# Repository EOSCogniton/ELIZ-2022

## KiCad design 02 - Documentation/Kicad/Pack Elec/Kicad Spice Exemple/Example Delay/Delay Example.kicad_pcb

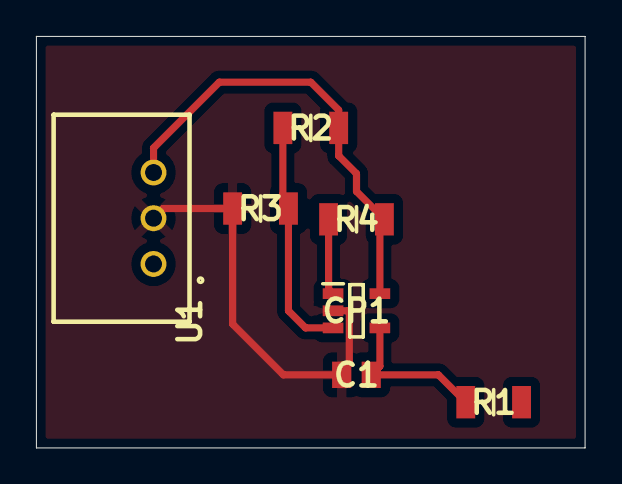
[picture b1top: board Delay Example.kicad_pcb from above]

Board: 2 copper layers, 30.5 x 22.9 mm, 7 parts (0 on the bottom side), 5 nets.

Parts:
C1: Condensateur 0805Y1000104JXT; CAPC2012X130N
CP1: Comparateur TS391ILT; SOT95P280X145-5N
R1, R2, R3, R4: Résistance RK73H2BLTDD2152F; RESC3216X70N
U1: Alim LP TSR_0.5-2450; TSR-0.5-2433

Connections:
0: C1.1, CP1.2 (VCC-), R3.1, U1.2 (GND)
unnamed: C1.2, CP1.4 (IN+), R1.1
unnamed: CP1.1 (OUT), R4.1
unnamed: CP1.3 (IN-), R2.1, R3.2
unnamed: CP1.5 (VCC+), R2.2, R4.2, U1.3 (+VOUT)

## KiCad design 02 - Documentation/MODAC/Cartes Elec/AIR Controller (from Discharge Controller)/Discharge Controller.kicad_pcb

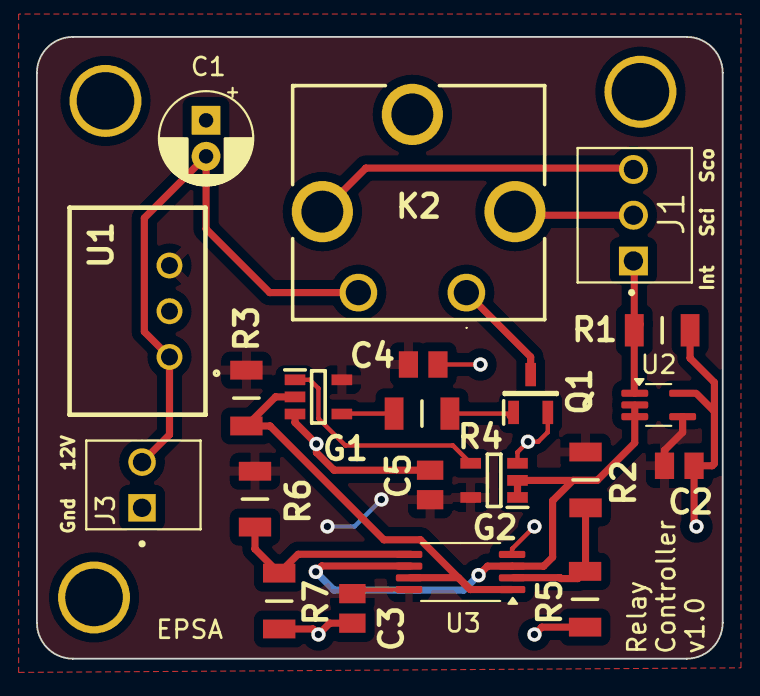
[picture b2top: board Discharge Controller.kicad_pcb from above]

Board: 2 copper layers, 38.1 x 34.5 mm, 21 parts (0 on the bottom side), 14 nets.

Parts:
C1: C; CP_Radial_D5.0mm_P2.00mm
C2, C3, C4, C5: 10n; CAPC2012X130N
G1: Gate AND SN74AHCT1G08DBVR; SOT95P280X145-5N
G2: Gate NAND SN74AHCT1G00DBVR; SOT95P280X145-5N
J1: 3P Droit 22-11-2032; MOLEX_22-11-2032
J3: 2P Droit 2-11-2022; MOLEX_22-11-2022
K2: Relais PCB; CP112V
Q1: NMOS SQ2348ES-T1_GE3; SOT95P237X112-3N
R1: 500k; RESC3216X70N
R2, R7: 82k; RESC3216X70N
R3: 10k; RESC3216X70N
R4: 1k; RESC3216X70N
R5, R6: 12k; RESC3216X70N
U1: Alim LP TSR_0.5-2450; TSR-0.5-2433
U2: SOT-353_SC-70-5_Handsoldering
U3: Opamp_Dual; TSSOP-8_4.4x3mm_P0.65mm

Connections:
+5V: C2.2, C3.2, C4.2, C5.2, G1.5 (VCC), G2.5 (VCC), R2.2, R3.1, R6.2, U1.3 (+VOUT), U2.4 (V+), U3.8 (V+)
+12V: C1.2, J3.2, K2.5, U1.1 (+VIN)
/0.75V: R2.1, R5.2, U3.2 (-)
/4.25V: R6.1, R7.2, U3.5 (+)
/Raw_Relay_Closed: J1.1, R1.1, U2.1 (+)
/Relay_Closed: G2.1, G2.2, U2.2 (-), U2.3, U3.3 (+), U3.6 (-)
/SC in: J1.2, K2.2
/SC out: J1.3, K2.4
/SCS_Compliance: G1.2, R3.2, U3.1, U3.7
GND: C1.1, C2.1, C3.1, C4.1, C5.1, G1.3 (GND), G2.3 (GND), J3.1, Q1.2, R1.2, R5.1, R7.1, U1.2 (GND), U2.5 (V-), U3.4 (V-)
unnamed: G1.1, G2.4
unnamed: G1.4, R4.1
unnamed: K2.1, Q1.3
unnamed: Q1.1, R4.2

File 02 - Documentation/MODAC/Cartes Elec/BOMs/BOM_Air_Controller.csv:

"Reference","Value","Qty","Manufacturer_Name","Manufacturer_Part_Number","Description"
"C1","C","1","","",""
"C2,C3,C4,C5","10n","4","Syfer","0805Y1000104JXT","Syfer 0805 Ceramic Chip Capacitors"
"G1,G2","Gate AND SN74AHCT1G08DBVR","2","Texas Instruments","SN74AHCT1G08DBVR","SN74AHCT1G08DBVR, Logic Gate 2 Input AND, AHCT, 8mA 5V 5-Pin SOT-23"
"J1","3P Droit 22-11-2032","1","Molex","22-11-2032",""
"J3","2P Droit 22-11-2022","1","Molex","22-11-2022",""
"K2","Relais PCB","1","Panasonic","CP1-12V","PANASONIC ELECTRIC WORKS - CP1-12V - RELAY, AUTOMOTIVE, SPDT, 14VDC, 20A"
"Q1","NMOS SQ2348ES-T1_GE3","1","Vishay","SQ2348ES-T1_GE3","VISHAY - SQ2348ES-T1_GE3 - MOSFET, AEC-Q101, N-CH, 30V, SOT-23"
"R1","500k","1","KOA Speer","RK73H2BLTDD2152F","Thick Film Resistors - SMD"
"R2,R7","82k","2","KOA Speer","RK73H2BLTDD2152F","Thick Film Resistors - SMD"
"R3","10k","1","KOA Speer","RK73H2BLTDD2152F","Thick Film Resistors - SMD"
"R4","1k","1","KOA Speer","RK73H2BLTDD2152F","Thick Film Resistors - SMD"
"R5,R6","12k","2","KOA Speer","RK73H2BLTDD2152F","Thick Film Resistors - SMD"
"U1","Alim LP TSR_0.5-2450","1","Traco Power","TSR 0.5-2450","0.5 Amp POL switching regulator, 4.75 to -32 VDC input, pos.-pos. circuit, LM78 compatible, SIP-3"
"U2","","1","Texas Instruments","TLV9061QDCKRQ1","Operational amplifier, single, node sequence=1:+ 2:- 3:OUT 4:V+ 5:V-"
"U3","Opamp_Dual","1","Texas Instruments","LMV393IPWR","Dual comparator"

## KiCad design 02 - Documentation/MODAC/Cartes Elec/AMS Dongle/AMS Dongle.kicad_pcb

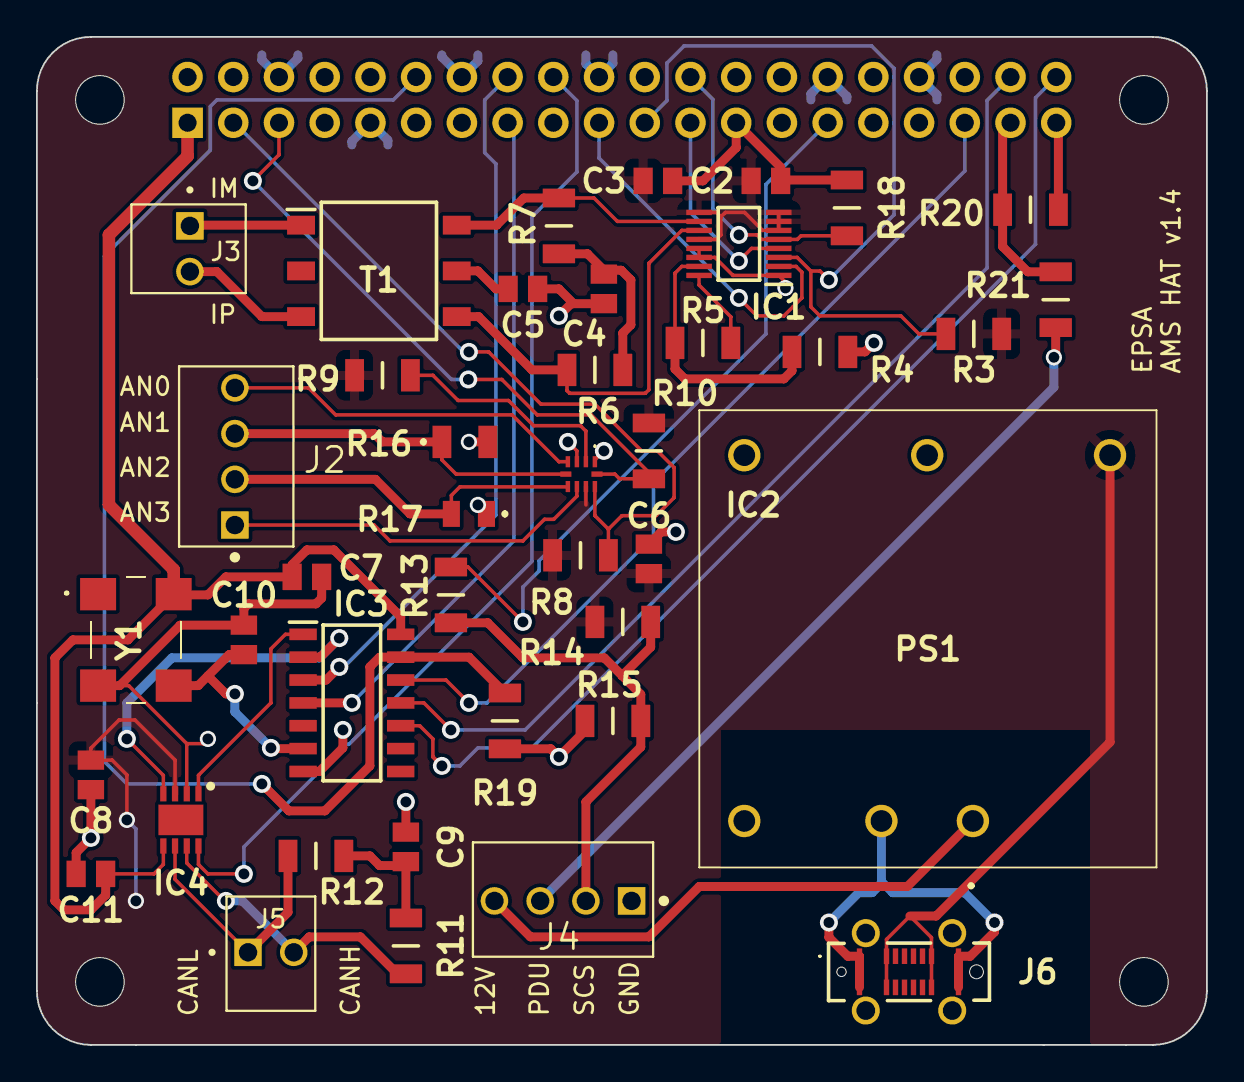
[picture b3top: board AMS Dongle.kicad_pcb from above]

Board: 2 copper layers, 65.0 x 56.0 mm, 46 parts (1 on the bottom side), 41 nets.

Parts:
C2, C3, C6, C7, C8, C11: 100n; CAPC2012X130N
C4, C5: 10n; CAPC2012X130N
C9: 4.7n; CAPC2012X130N
C10: 22p; CAPC2012X130N
IC1: LTC6820HMS#PBF; SOP50P490X110-16N
IC2: ADC I2C ADS1115QNKSRQ1; ADS1115QNKSRQ1
IC3: CAN Controller MCP2518FDT-H_SL; SOIC127P600X175-14N
IC4: CAN Transceiver ATA6563-GBQW1; SON65P300X300X90-9N-D
J1: GPIO; PinSocket_2x20_P2.54mm_Vertical
J2, J4: 4P Angle 171857-4004; MOLEX_22-11-2042
J3, J5: 2P Angle 171857-4002; MOLEX_22-11-2022
J6: UJ20-C-V-C-1-SMT-TR; UJ20CVC1SMTTR
MH1, MH2, MH3, MH4: MountingHole_2.7mm_M2.5
PS1: Alim; THN301211
R3, R8, R9, R10: 2k; RESC3216X70N
R4, R5: 1k; RESC3216X70N
R6, R7: 51; RESC3216X70N
R11, R12: 60; RESC3216X70N
R13: 3k9; RESC3216X70N
R14, R15: 8k2; RESC3216X70N
R16: 24 .5W; RCS1206_E3
R17: 47 .5W; RCS0805_E3
R18, R19: 360; RESC3216X70N
R20: 3.6k; RESC3216X70N
R21: 10k; RESC3216X70N
T1: SM91502ALE; SOP254P927X572-6N
Y1: Oscillateur CB3-3C-20M0000; CB3LV3C20M0000

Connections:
+3V3: C7.1, C11.1, IC3.14 (VDD), IC4.5 (VIO), J1.1, J1.17, Y1.4 (VCC)
+5V: C2.1, C3.1, C6.1, C8.2, IC1.6 (VDDS), IC1.7 (POL), IC1.8 (PHA), IC1.9 (VDD), IC1.12 (MSTR), IC2.8 (VDD), IC4.3 (VCC), J6.A4 (VBUS_1), J6.A9 (VBUS_2), J6.B4 (VBUS_3), J6.B9 (VBUS_4), PS1.3 (+VOUT), R3.1, R8.2, R9.1, R10.2, R14.2
+5VP: J1.2, J1.4
+12V: J4.4, PS1.1 (+VIN_(VCC))
/AN0: IC2.4 (AIN0), J2.4
/AN1: IC2.5 (AIN1), J2.3, R16.1
/AN2: IC2.6 (AIN2), J2.2, R17.2
/AN3: IC2.7 (AIN3), J2.1
/CANH: IC4.7 (CANH), J5.2, R11.2
/CANL: IC4.6 (CANL), J5.1, R12.2
/GPIO2/SDA1: IC2.9 (SDA), J1.3, R8.1
/GPIO3/SCL1: IC2.10 (SCL), J1.5, R10.1
/GPIO5: J1.29, R13.2
/GPIO8/SPI0.CE0: IC1.5 (~CS), J1.24, R18.2
/GPIO9/SPI0.MISO: IC1.3 (MISO), J1.21, R3.2
/GPIO10/SPI0.MOSI: IC1.2 (MOSI), J1.19
/GPIO11/SPI0.SCLK: IC1.4 (SCK), J1.23
/GPIO18/PCM.CLK/SPI1.CE0: IC3.13 (NCS), J1.12, R19.1
/GPIO19/PCM.FS/SPI1.MISO: IC3.12 (SDO), J1.35
/GPIO20/PCM.DIN/SPI1.MOSI: IC3.11 (SDI), J1.38
/GPIO21/PCM.DOUT/SPI1.SCLK: IC3.10 (SCK), J1.40
/GPIO22: IC3.4 (~INT), J1.15
/GPIO23: IC3.3 (CLKO/SOF), J1.16
/GPIO24: IC4.8 (STBY), J1.18
/GPIO26: J1.37, R20.2, R21.1
/IM: J3.1, T1.1 (PRI_1)
/IP: J3.2, T1.3 (PRI_3)
/PDU: J4.3, R21.2
/SCS Out: J4.2, R13.1, R14.1, R15.2
GND: C2.2, C3.2, C4.1, C5.2, C6.2, C7.2, C8.1, C9.2, C10.2, C11.2, IC1.1 (EN), IC1.13 (SLOW), IC1.14 (GND), IC2.1 (ADDR), IC2.3 (GND), IC3.7 (VSS), IC4.2 (GND), J1.6, J1.9, J1.14, J1.20, J1.25, J1.30, J1.34, J1.39, J4.1, J6.A1 (GND_1), J6.A12 (GND_2), J6.B1 (GND_3), J6.B12 (GND_4), PS1.2 (-VIN_(GND)), PS1.5 (-VOUT), R4.2, R15.1, R16.2, R17.1, R18.1, R19.2, R20.1, Y1.2 (GND)
unnamed: C4.2, R6.2, R7.1
unnamed: C9.1, R11.1, R12.1
unnamed: IC1.16 (IBIAS), R5.2
unnamed: IC1.15 (ICMP), R4.1, R5.1
unnamed: IC1.10 (IM), R7.2, T1.6 (SEC_3)
unnamed: IC1.11 (IP), R6.1, T1.4 (SEC_1)
unnamed: IC2.2 (ALERT/RDY), R9.2
unnamed: C10.1, IC3.6 (OSC1), Y1.3 (OUTPUT)
unnamed: IC3.2 (RXCAN), IC4.4 (RXD)
unnamed: IC3.1 (TXCAN), IC4.1 (TXD)
unnamed: C5.1, T1.5 (SEC_2)

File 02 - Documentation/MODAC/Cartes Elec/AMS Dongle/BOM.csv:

"Reference","Value","Manufacturer_Name","Manufacturer_Part_Number","Mouser Part Number","Mouser Price/Stock","Qty"
"C2,C3,C6,C7,C8","100n","Syfer","0805Y1000104JXT","","","5"
"C4,C5","10n","Syfer","0805Y1000104JXT","","","2"
"C9","4.7n","Syfer","0805Y1000104JXT","","","1"
"C10","22p","Syfer","0805Y1000104JXT","","","1"
"IC1","LTC6820HMS#PBF","Analog Devices","LTC6820HMS#PBF","584-LTC6820HMS#PBF","https://www.mouser.co.uk/ProductDetail/Analog-Devices/LTC682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","1"
"IC2","ADC I2C ADS1115QNKSRQ1","Texas Instruments","ADS1115QNKSRQ1","595-ADS1115QNKSRQ1","https://www.mouser.co.uk/ProductDetail/Texas-Instruments/ADS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","1"
"IC3","CAN Controller MCP2518FDT-H_SL","Microchip","MCP2518FDT-H/SL","579-MCP2518FDT-H/SL","https://www.mouser.co.uk/ProductDetail/Microchip-Technology/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","1"
"IC4","CAN Transceiver BD41041FJ-CE2","ROHM Semiconductor","BD41041FJ-CE2","755-BD41041FJ-CE2","https://www.mouser.co.uk/ProductDetail/ROHM-Semiconductor/BD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","1"
"J1","GPIO","","","","","1"
"J2,J4","4P Angle 171857-4004","Molex","171857-4004","538-171857-4004","https://www.mouser.co.uk/ProductDetail/Molex/171857-4004?qs=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","2"
"J3,J5","2P Angle 171857-4002","Molex","171857-4002","538-171857-4002","https://www.mouser.co.uk/ProductDetail/Molex/171857-4002?qs=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","2"
"J6","Connecteur USB-C USB4720-03-A","GCT (GLOBAL CONNECTOR TECHNOLOGY)","USB4720-03-A","640-USB472003A","https://www.mouser.co.uk/ProductDetail/GCT/USB4720-03-A?qs=Z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","1"
"PS1","Alim","Traco Power","THN 30-1211","495-THN-30-1211","https://www.mouser.co.uk/ProductDetail/TRACO-Power/THN-30-12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","1"
"Q1","NMOS SQ2348ES-T1_GE3","Vishay","SQ2348ES-T1_GE3","781-SQ2348ES-T1_GE3","https://www.mouser.co.uk/ProductDetail/Vishay-Siliconix/SQ23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","1"
"R3,R8,R9,R10","2k","KOA Speer","RK73H2BLTDD2152F","N/A","https://www.mouser.co.uk/ProductDetail/KOA-Speer/RK73H2BLTDD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","4"
"R4","2.8k","KOA Speer","RK73H2BLTDD2152F","N/A","https://www.mouser.co.uk/ProductDetail/KOA-Speer/RK73H2BLTDD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","1"
"R5","1.21k","KOA Speer","RK73H2BLTDD2152F","N/A","https://www.mouser.co.uk/ProductDetail/KOA-Speer/RK73H2BLTDD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","1"
"R6,R7","51","KOA Speer","RK73H2BLTDD2152F","N/A","https://www.mouser.co.uk/ProductDetail/KOA-Speer/RK73H2BLTDD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","2"
"R11,R12","60","KOA Speer","RK73H2BLTDD2152F","N/A","https://www.mouser.co.uk/ProductDetail/KOA-Speer/RK73H2BLTDD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","2"
"R13","3k9","KOA Speer","RK73H2BLTDD2152F","N/A","https://www.mouser.co.uk/ProductDetail/KOA-Speer/RK73H2BLTDD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","1"
"R14,R15","8k2","KOA Speer","RK73H2BLTDD2152F","N/A","https://www.mouser.co.uk/ProductDetail/KOA-Speer/RK73H2BLTDD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","2"
"S1,S2","CAS-120B","Nidec Copal","CAS-120B","229-CAS-120B","https://www.mouser.co.uk/ProductDetail/Nidec-Copal/CAS-120B?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","2"
"T1","SM91502ALE","Bourns","SM91502ALE","652-SM91502ALE","https://www.mouser.co.uk/ProductDetail/Bourns/SM91502ALE?qs=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","1"
"Y1","Oscillateur CB3-3C-20M0000","CTS","CB3-3C-20M0000","774-CB3-3C-20M0","https://www.mouser.co.uk/ProductDetail/CTS-Electronic-Compon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","1"

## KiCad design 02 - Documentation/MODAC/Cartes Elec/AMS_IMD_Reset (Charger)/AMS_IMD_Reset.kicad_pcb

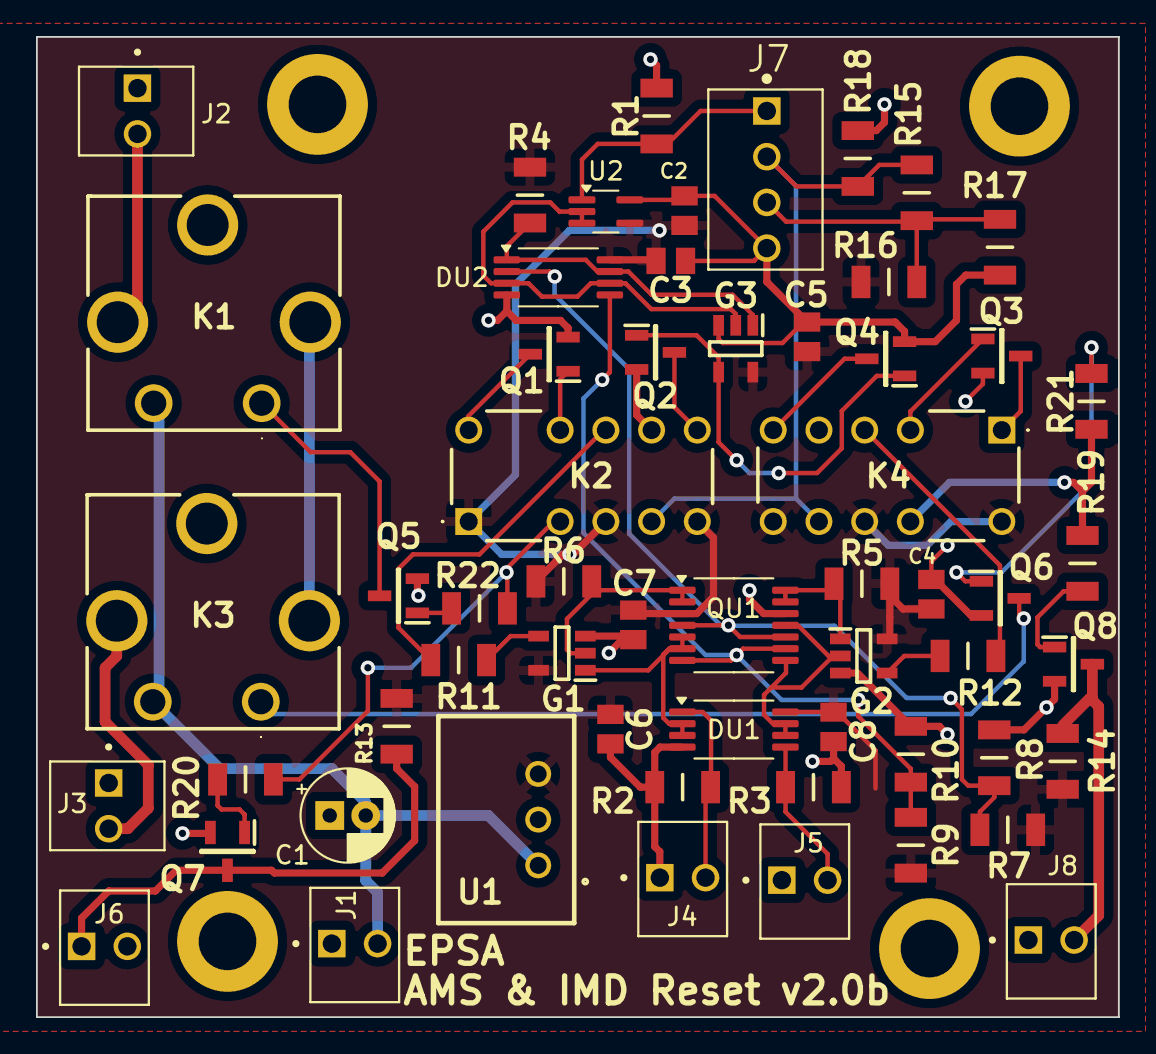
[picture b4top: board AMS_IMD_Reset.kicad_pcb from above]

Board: 2 copper layers, 60.1 x 54.5 mm, 58 parts (0 on the bottom side), 40 nets.

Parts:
C1: C; CP_Radial_D5.0mm_P2.00mm
C2, C3, C4, C5, C6, C7, C8: 1u; CAPC2012X130N
DU1, DU2: Opamp_Dual; TSSOP-8_4.4x3mm_P0.65mm
G1, G2: Gate NAND SN74AHCT1G00DBVR; SOT95P280X145-5N
G3: Gate AND SN74AHCT1G08DBVR; SOT95P280X145-5N
J1, J2, J3, J4, J5, J6, J8: 2P Droit 2-11-2022; MOLEX_22-11-2022
J7: 4P Droit 22-11-2042; MOLEX_22-11-2042
K1, K3: Relais PCB; CP112V
K2, K4: Bistable V23079B1201B301; V23079B1201B301
Q1, Q2, Q3, Q4, Q5, Q6, Q7, Q8: NMOS SQ2348ES-T1_GE3; SOT95P237X112-3N
QU1: Opamp_Quad; TSSOP-14_4.4x5mm_P0.65mm
R1, R2, R3: 500k; RESC3216X70N
R4, R5, R6, R13, R14: 10k; RESC3216X70N
R7, R10: 82k; RESC3216X70N
R8, R9: 12k; RESC3216X70N
R11, R12: 500; RESC3216X70N
R15: 3k9; RESC3216X70N
R16, R17: 8k2; RESC3216X70N
R18: 100k; RESC3216X70N
R19, R20, R21, R22: 1k; RESC3216X70N
U1: Alim LP TSR_0.5-2450; TSR-0.5-2433
U2: SOT-353_SC-70-5_Handsoldering

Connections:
+5V: C2.1, C3.2, C4.2, C5.2, C6.1, C7.1, C8.1, DU1.8 (V+), DU2.8 (V+), G1.5 (VCC), G2.5 (VCC), G3.5 (VCC), K2.1 (COIL1), K2.4 (COM_1), K2.6 (COIL2), K4.7 (COIL2), K4.9 (COM_2), K4.12 (COIL1), QU1.3 (V+), R4.1, R5.2, R6.1, R7.2, R9.2, R13.1, R14.1, R16.2, U1.3 (+VOUT), U2.4 (V+)
+12V: C1.2, J1.2, K1.5, K3.5, U1.1 (+VIN)
/0.75V: DU2.2 (-), QU1.4 (-), QU1.10 (-), R7.1, R8.2
/4.25V: DU2.5 (+), QU1.7 (+), QU1.9 (+), R9.1, R10.2
/AMS_OK: DU1.6 (-), DU1.7, G2.2, QU1.8 (-), QU1.11 (+)
/AMS_SCS_Compliance: G2.1, QU1.13, QU1.14, R5.1
/Button_Input: J7.2, K2.5 (Set_1), K4.8 (Set_2), R15.1, R18.1
/Button_Input_SCS: J7.3, R15.2, R16.1, R17.2
/Button_Output: DU2.3 (+), DU2.6 (-), G3.2, U2.2 (-), U2.3
/Button_Output_SCS_Compliance: DU2.1, DU2.7, G3.1, R4.2
/IMD_OK: DU1.2 (-), DU1.3, G1.1, QU1.5 (+), QU1.6 (-)
/IMD_SCS_Compliance: G1.2, QU1.1, QU1.2, R6.2
/Raw_AMS_OK: DU1.5 (+), J5.2, R3.1
/Raw_Button_Output: J7.1, R1.1, U2.1 (+)
/Raw_IMD_OK: DU1.1 (+), J4.2, R2.1
/SC in: J2.2, K1.4
/SC out: J3.2, K3.4
/SC_Closed_AMS: K4.10 (Reset_2), R19.1, R21.1
/SC_Closed_IMD: K2.3 (Reset_1), R20.1, R22.1
GND: C1.1, C2.2, C3.1, C4.1, C5.1, C6.2, C7.2, C8.2, DU1.4 (V-), DU2.4 (V-), G1.3 (GND), G2.3 (GND), G3.3 (GND), J1.1, J2.1, J3.1, J4.1, J5.1, J6.2, J7.4, J8.1, K2.8 (Set_2), K4.5 (Set_1), Q1.2, Q2.2, Q3.2, Q4.2, Q5.2, Q6.2, Q7.2, Q8.2, QU1.12 (V-), R1.2, R2.2, R3.2, R8.1, R10.1, R17.1, R18.2, U1.2 (GND), U2.5 (V-)
unnamed: G1.4, R11.1
unnamed: G2.4, R12.1
unnamed: G3.4, Q2.1, Q4.1
unnamed: J6.1, Q7.3, R13.2
unnamed: J8.2, Q8.3, R14.2
unnamed: K1.1, Q5.3
unnamed: K1.2, K3.2
unnamed: K2.12 (COIL1), Q1.3
unnamed: K2.7 (COIL2), Q2.3
unnamed: K2.9 (COM_2), R11.2
unnamed: K2.10 (Reset_2), Q1.1
unnamed: K3.1, Q6.3
unnamed: K4.1 (COIL1), Q3.3
unnamed: K4.6 (COIL2), Q4.3
unnamed: K4.4 (COM_1), R12.2
unnamed: K4.3 (Reset_1), Q3.1
unnamed: Q5.1, R22.2
unnamed: Q6.1, R21.2
unnamed: Q7.1, R20.2
unnamed: Q8.1, R19.2

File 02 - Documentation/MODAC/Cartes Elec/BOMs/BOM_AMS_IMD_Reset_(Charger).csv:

"Reference","Value","Qty","Manufacturer_Name","Manufacturer_Part_Number","Mouser Part Number","Mouser Price/Stock"
"C1","C","1","","","",""
"C2,C3,C4,C5,C6,C7,C8","1u","7","Syfer","0805Y1000104JXT","",""
"DU1","Opamp_Dual","1","Texas Instruments","TLV9062QPWRQ1 ","595-TLV9062QPWRQ1 ",""
"DU2","Opamp_Dual","1","Texas Instruments","LMV393IPWR","595-LMV393IPWR",""
"G1,G2","Gate NAND SN74AHCT1G00DBVR","2","Texas Instruments","SN74AHCT1G00DBVR","595-SN74AHCT1G00DBVR","https://www.mouser.co.uk/ProductDetail/Texas-Instruments/SN7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"
"G3","Gate AND SN74AHCT1G08DBVR","1","Texas Instruments","SN74AHCT1G08DBVR","595-SN74AHCT1G08DBVR","https://www.mouser.co.uk/ProductDetail/Texas-Instruments/SN7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"
"J1,J2,J3,J4,J5,J6","2P Droit 2-11-2022","6","Molex","22-11-2022","538-22-11-2022","https://www.mouser.fr/ProductDetail/Molex/22-11-2022?qs=mrPi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"
"J7","4P Droit 22-11-2042","1","Molex","22-11-2042","538-22-11-2042","https://www.mouser.fr/ProductDetail/Molex/22-11-2042?qs=mrPi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"
"K1,K3","Relais PCB","2","Panasonic","CP1-12V","769-CP1-12V","https://www.mouser.co.uk/ProductDetail/Panasonic-Industrial-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"
"K2,K4","Bistable V23079B1201B301","2","TE Connectivity","V23079B1201B301","655-V23079B1201B301","https://www.mouser.co.uk/ProductDetail/TE-Connectivity-Axico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"
"Q1,Q2,Q3,Q4,Q5,Q6,Q7,Q8","NMOS SQ2348ES-T1_GE3","8","Vishay","SQ2348ES-T1_GE3","781-SQ2348ES-T1_GE3","https://www.mouser.co.uk/ProductDetail/Vishay-Siliconix/SQ23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"
"QU1","Opamp_Quad","1","Texas Instruments","LMV339IPWR","595-LMV339IPWR",""
"R1,R2,R3","500k","3","KOA Speer","RK73H2BLTDD2152F","N/A","https://www.mouser.co.uk/ProductDetail/KOA-Speer/RK73H2BLTDD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"
"R4,R5,R6,R13,R14","10k","5","KOA Speer","RK73H2BLTDD2152F","N/A","https://www.mouser.co.uk/ProductDetail/KOA-Speer/RK73H2BLTDD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"
"R7,R10","82k","2","KOA Speer","RK73H2BLTDD2152F","N/A","https://www.mouser.co.uk/ProductDetail/KOA-Speer/RK73H2BLTDD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"
"R8,R9","12k","2","KOA Speer","RK73H2BLTDD2152F","N/A","https://www.mouser.co.uk/ProductDetail/KOA-Speer/RK73H2BLTDD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"
"R11,R12","500","2","KOA Speer","RK73H2BLTDD2152F","N/A","https://www.mouser.co.uk/ProductDetail/KOA-Speer/RK73H2BLTDD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"
"R15","3k9","1","KOA Speer","RK73H2BLTDD2152F","N/A","https://www.mouser.co.uk/ProductDetail/KOA-Speer/RK73H2BLTDD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"
"R16,R17","8k2","2","KOA Speer","RK73H2BLTDD2152F","N/A","https://www.mouser.co.uk/ProductDetail/KOA-Speer/RK73H2BLTDD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"
"R18","100k","1","KOA Speer","RK73H2BLTDD2152F","N/A","https://www.mouser.co.uk/ProductDetail/KOA-Speer/RK73H2BLTDD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"
"U1","Alim LP TSR_0.5-2450","1","Traco Power","TSR 0.5-2450","495-TSR0.5-2450","https://www.mouser.co.uk/ProductDetail/TRACO-Power/TSR-0.5-2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"
"U2","","1","Texas Instruments","TLV9061QDCKRQ1 "," 595-TLV9061QDCKRQ1 ",""

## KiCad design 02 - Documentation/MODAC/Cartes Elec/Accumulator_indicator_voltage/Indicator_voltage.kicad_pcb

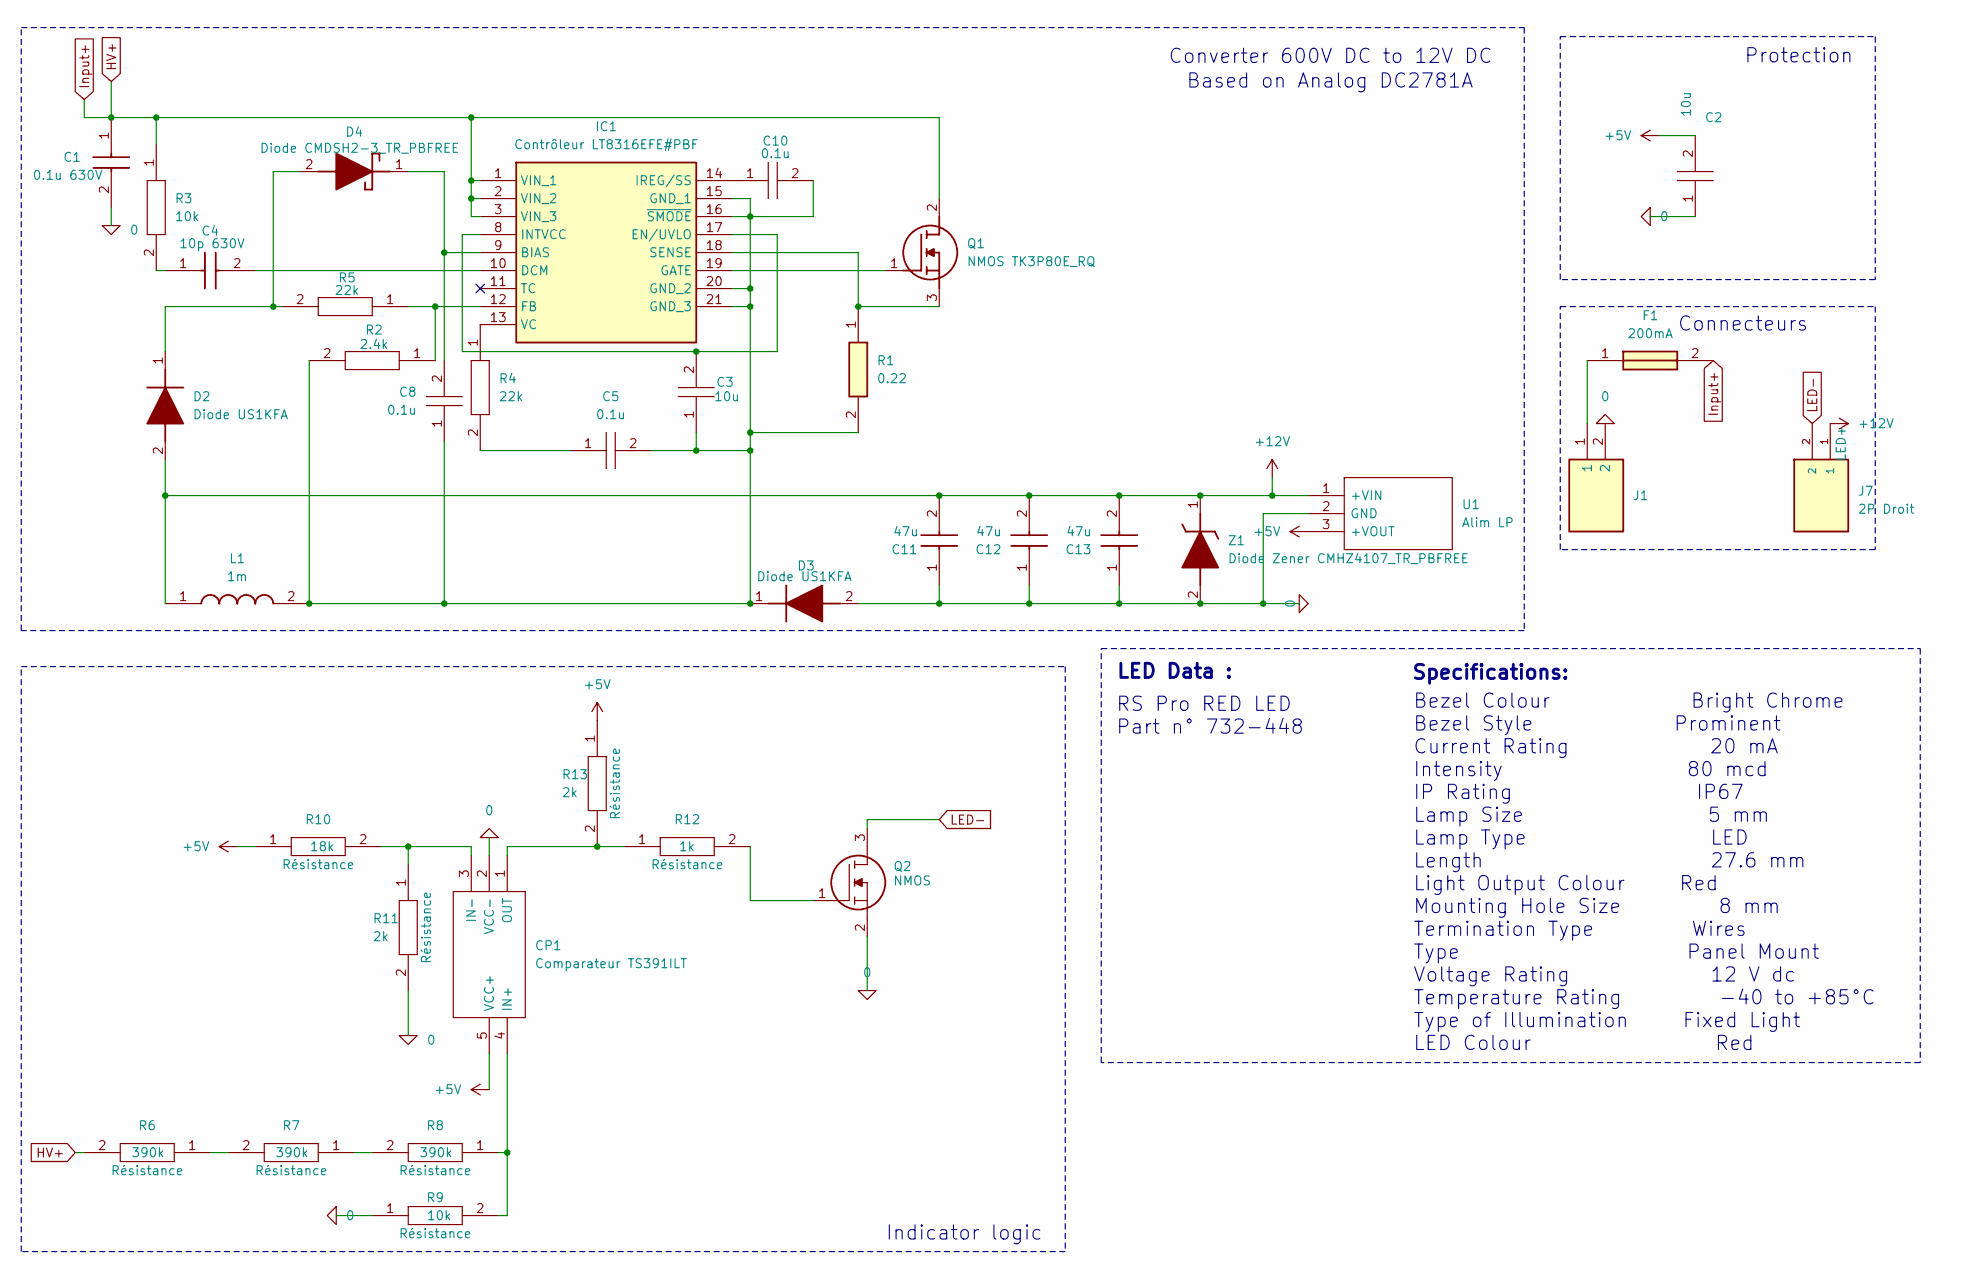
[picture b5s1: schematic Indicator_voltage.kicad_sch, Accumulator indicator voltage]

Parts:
C1: 0.1u 630V; CAPC4532X200N; Mouser Part Number 81-GCJ43DR72J104KX1L
C2, C3: 10u; CAPC2012X130N; Manufacturer_Part_Number 0805Y1000104JXT
C4: 10p 630V; CAPC3216X100N; Mouser Part Number 81-GRM31A5C2J100JW1D
C5, C8, C10: 0.1u; CAPC2012X130N; Manufacturer_Part_Number 0805Y1000104JXT
C11, C12, C13: 47u; CAPC3225X270N; Mouser Part Number 81-GRM32ER61C476KE5K
CP1: Comparateur TS391ILT; SOT95P280X145-5N; Manufacturer_Part_Number TS391ILT; Mouser Part Number 511-TS391IL
D2, D3: Diode US1KFA; SODFL3618X143N; Mouser Part Number 512-US1KFA
D4: Diode CMDSH2-3_TR_PBFREE; SOD2512X110N; Mouser Part Number 610-CMDSH2-3
F1: 200mA; 0ADAP0200RE; Mouser Part Number 530-0ADAP0200-RE
IC1: Contrôleur LT8316EFE#PBF; LT8315EFEPBF; Mouser Part Number 584-LT8316EFE#PBF
J1: 2P Angle HV 200241-1212; 2002411212; Mouser Part Number 538-200241-1212
J7: 2P Droit 2-11-2022; MOLEX_22-11-2022; PARTREV BD8; Mouser Part Number 538-22-11-2022
L1: 1m; WE-PD_1260_1245_1280_121054; Mouser Part Number 710-7447709102
Q1: NMOS TK3P80E_RQ; TK3P80ERQ; Manufacturer_Part_Number TK3P80E,RQ
Q2: NMOS SQ2348ES-T1_GE3; SOT95P237X112-3N; Manufacturer_Part_Number SQ2348ES-T1_GE3; Mouser Part Number 781-SQ2348ES-T1_GE3
R1: 0.22; RESC1608X55N; Mouser Part Number 754-RL0816S-R22-F
R2: 2.4k; RESC3216X70N; Manufacturer_Part_Number RK73H2BLTDD2152F; Mouser Part Number N/A
R3, R9: 10k; RESC3216X70N; Manufacturer_Part_Number RK73H2BLTDD2152F; Mouser Part Number N/A
R4, R5: 22k; RESC3216X70N; Manufacturer_Part_Number RK73H2BLTDD2152F; Mouser Part Number N/A
R6, R7, R8: 390k; RESC3216X70N; Manufacturer_Part_Number RK73H2BLTDD2152F; Mouser Part Number N/A
R10: 18k; RESC3216X70N; Manufacturer_Part_Number RK73H2BLTDD2152F; Mouser Part Number N/A
R11, R13: 2k; RESC3216X70N; Manufacturer_Part_Number RK73H2BLTDD2152F; Mouser Part Number N/A
R12: 1k; RESC3216X70N; Manufacturer_Part_Number RK73H2BLTDD2152F; Mouser Part Number N/A
U1: Alim LP TSR_0.5-2450; TSR-0.5-2433; Manufacturer_Part_Number TSR 0.5-2450; Mouser Part Number 495-TSR0.5-2450
Z1: Diode Zener CMHZ4107_TR_PBFREE; SOD3816X135N; Manufacturer_Part_Number CMHZ4107 TR PBFREE

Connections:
0: C1.2, C2.1, C11.1, C12.1, C13.1, CP1.2 (VCC-), D3.2 (A), J1.2, Q2.2, R9.1, R11.2, U1.2 (GND), Z1.2 (A)
+5V: C2.2, CP1.5 (VCC+), R10.1, R13.1, U1.3 (+VOUT)
+12V: C11.2, C12.2, C13.2, D2.2 (A), J7.1, L1.1, U1.1 (+VIN), Z1.1 (K)
HV+: C1.1, F1.2, IC1.1 (VIN_1), IC1.2 (VIN_2), IC1.3 (VIN_3), Q1.2 (D), R3.1, R6.2
LED-: J7.2, Q2.3
unnamed: C4.1, R3.2
unnamed: C5.1, R4.2
unnamed: CP1.4 (IN+), R8.1, R9.2
unnamed: CP1.3 (IN-), R10.2, R11.1
unnamed: CP1.1 (OUT), R12.1, R13.2
unnamed: D2.1 (K), D4.2 (A), R5.2
unnamed: C3.1, C5.2, C8.1, C10.2, D3.1 (K), IC1.15 (GND_1), IC1.16 (~SMODE), IC1.20 (GND_2), IC1.21 (GND_3), L1.2, R1.2, R2.2
unnamed: C8.2, D4.1 (K), IC1.9 (BIAS)
unnamed: F1.1, J1.1
unnamed: C4.2, IC1.10 (DCM)
unnamed: C3.2, IC1.8 (INTVCC), IC1.17 (EN/UVLO)
unnamed: IC1.12 (FB), R2.1, R5.1
unnamed: IC1.19 (GATE), Q1.1 (G)
unnamed: C10.1, IC1.14 (IREG/SS)
unnamed: IC1.18 (SENSE), Q1.3 (S), R1.1
unnamed: IC1.13 (VC), R4.1
unnamed: Q2.1, R12.2
unnamed: R6.1, R7.2
unnamed: R7.1, R8.2

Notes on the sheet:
Protection
Based on Analog DC2781A
RS Pro RED LED Part n° 732-448
Indicator logic
LED Data :
Specifications:
Connecteurs
Converter 600V DC to 12V DC
Bezel Colour Bright Chrome Bezel Style Prominent Current Rating 20 mA Intensity 80 mcd IP Rating IP67 Lamp Size 5 mm Lamp Type LED Length 27.6 mm Light Output Colour Red Mounting Hole Size 8 mm Termination Type Wires Type Panel Mount Voltage Rating 12 V dc Temperature Rating -40 to +85°C Type of Il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

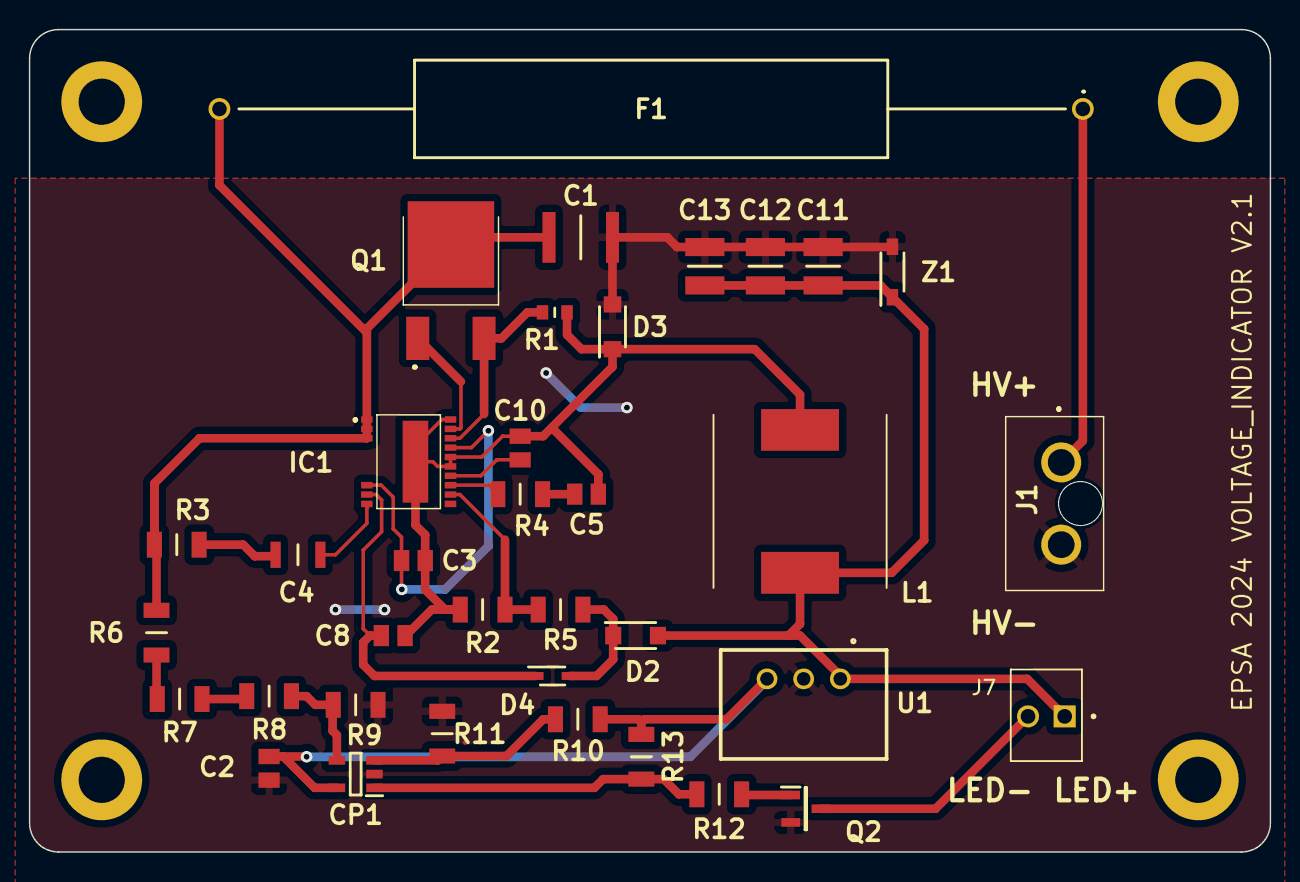
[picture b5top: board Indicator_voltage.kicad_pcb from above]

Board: 2 copper layers, 86.0 x 57.0 mm, 36 parts (0 on the bottom side), 24 nets.

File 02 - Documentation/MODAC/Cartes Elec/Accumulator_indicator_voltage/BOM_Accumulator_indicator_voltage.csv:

"Reference","Value","Qty","Manufacturer_Name","Manufacturer_Part_Number","Description"
"C1","0.1u 630V","1","Murata Electronics","GCJ43DR72J104KXJ1L","Capacitor GCJ43 L=4.5mm W=3.2mm T=2.0mm 1812"
"C2,C3","10u","2","Syfer","0805Y1000104JXT","Syfer 0805 Ceramic Chip Capacitors"
"C4","10p 630V","1","Murata Electronics","GRM31A5C2J100JW01D","Capacitor GRM31_0.20 L=3.2mm W=1.6mm T=1.0mm 1205"
"C5,C8,C10","0.1u","3","Syfer","0805Y1000104JXT","Syfer 0805 Ceramic Chip Capacitors"
"C11,C12,C13","47u","3","Murata Electronics","GRM32ER61C476KE15K","Murata 1210 GRM 47uF Ceramic Multilayer Capacitor, 16 V, +85C, X5R Dielectric, +/-10% SMD"
"CP1","Comparateur TS391ILT","1","STMicroelectronics","TS391ILT","TS391ILT, Comparator Open Collector 0.3us 12 V, 15 V, 18 V, 24 V, 28 V, 3 V, 5 V, 9 V 5-Pin SOT-23"
"D2,D3","Diode US1KFA","2","onsemi","US1KFA","Diode Switching 800V 1A 2-Pin SOD-123FA T/R"
"D4","Diode CMDSH2-3_TR_PBFREE","1","Central Semiconductor","CMDSH2-3 TR PBFREE","DIODE SCHOTTKY 30V 200MA SOD323"
"F1","200mA","1","BelFuse","0ADAP0200-RE","Fuses with Leads (Through Hole) FUSE, CERAMIC TUBE 0.2A 600VAC600VDC"
"IC1","Contrôleur LT8316EFE#PBF","1","Analog Devices","LT8316EFE#PBF","Switching Controllers 600VIN Micropower, Isolated No-Opto Flyb"
"J1","2P Angle HV 200241-1212","1","Molex","200241-1212","Headers & Wire Housings"
"J7","2P Droit 2-11-2022","1","Molex","22-11-2022",""
"L1","1m","1","Wurth Elektronik","7447709102","SMD-Shielded Power Inductors WE-PD"
"Q1","NMOS TK3P80E_RQ","1","Toshiba","TK3P80E,RQ","MOSFET PWR MOS PD=80W  F=1MHZ"
"Q2","NMOS SQ2348ES-T1_GE3","1","Vishay","SQ2348ES-T1_GE3","VISHAY - SQ2348ES-T1_GE3 - MOSFET, AEC-Q101, N-CH, 30V, SOT-23"
"R1","0.22","1","Susumu","RL0816S-R22-F","220 mOhms +/-1% 0.2W, 1/5W Chip Resistor 0603 (1608 Metric) Current Sense Thin Film"
"R2","2.4k","1","KOA Speer","RK73H2BLTDD2152F","Thick Film Resistors - SMD"
"R3,R9","10k","2","KOA Speer","RK73H2BLTDD2152F","Thick Film Resistors - SMD"
"R4,R5","22k","2","KOA Speer","RK73H2BLTDD2152F","Thick Film Resistors - SMD"
"R6,R7,R8","390k","3","KOA Speer","RK73H2BLTDD2152F","Thick Film Resistors - SMD"
"R10","18k","1","KOA Speer","RK73H2BLTDD2152F","Thick Film Resistors - SMD"
"R11,R13","2k","2","KOA Speer","RK73H2BLTDD2152F","Thick Film Resistors - SMD"
"R12","1k","1","KOA Speer","RK73H2BLTDD2152F","Thick Film Resistors - SMD"
"U1","Alim LP TSR_0.5-2450","1","Traco Power","TSR 0.5-2450","0.5 Amp POL switching regulator, 4.75 to 32 VDC input, pos.-pos. circuit, LM78 compatible, SIP-3"
"Z1","Diode Zener CMHZ4107_TR_PBFREE","1","Central Semiconductor","CMHZ4107 TR PBFREE","Zener Diodes 500mW 5% Tolerance"
